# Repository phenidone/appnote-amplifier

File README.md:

# appnote-amplifier

This is a PCB design for a headphone amplifier based on the example schematic in the LME49600 datasheet.

## Power Supply

You will need a 12VAC or 24VAC centre-tapped transformer.  The simplest/safest option is to use it with
a Class-II (double insulated) accredited 12VAC 0.5A plugpack and not ground any part of this design.

Use Phoenix-style screw terminals.

## Inputs & Outputs

Place a 10K dual-gang A-scale volume pot between the signal source and the inputs to this board.  Use 0.1"-pitch
Phoenix-style screw terminals.

## Thermal

There is a bare patch on the board surrounding the output stage; you can solder a strip of copper
sheet here to act as a heatsink, if that seems to be necessary (almost certainly not).  Note that it will be connected to the negative
rail, so don't let the heatsink touch anything.

## Errata

Rev.A is missing reverse-protection diodes around the regulators.  They are considered best-practise
for cases where the input voltage on a regulator may collapse faster than its output and as such should not be necessary for this design - the regulators should be the only current
drain upon the rectifier capacitors.  They have been added to Rev.B on the basis of paranoia and can be hand-soldered onto the underside of a Rev.A board.

The BOM lists 7812 and 7912 regulators and 12VAC supply, which is more voltage than most headphones require.  For headphones of no more than 64 ohms,
a 7805 and 7905 are enough and will need only a 6VAC transformer.

## License

This hardware design is (C) 2017 William Brodie-Tyrrell and is licensed under the CERN OHL; see cern_ohl_v_1_2.pdf

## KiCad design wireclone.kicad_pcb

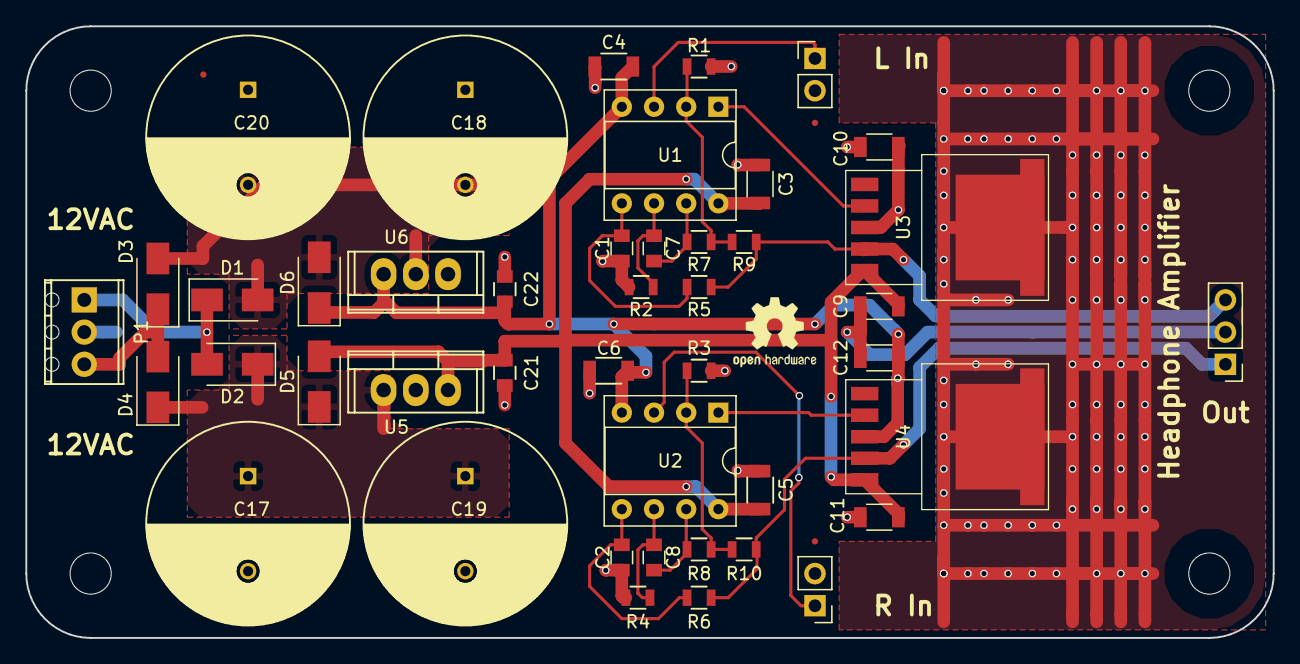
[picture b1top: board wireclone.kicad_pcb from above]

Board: 2 copper layers, 98.4 x 48.3 mm, 48 parts (0 on the bottom side), 21 nets.

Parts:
C1, C2, C7, C8: 1u; C_0805
C3, C4, C5, C6: 1u; C_1206
C9, C10, C11, C12: 10u; C_1206
C17, C18, C19, C20: 1000u; C_Radial_D16_L25_P7.5
C21, C22: 100n; C_0805
D1, D2, D3, D4, D5, D6: M7; D_SMA
FID1, FID2, FID3, FID4: FIDUCIAL; FID0.5
P1: CONN_01X03; TerminalBlock_Phoenix_MPT-2.54mm_3pol
P2, P4: CONN_01X02; Pin_Header_Straight_1x02_Pitch2.54mm
P3: CONN_01X03; Pin_Header_Straight_1x03_Pitch2.54mm
R1, R3, R7, R8, R9, R10: 1k; R_0805
R2, R4, R5, R6: 1M; R_0805
U1, U2: LME49720; DIP-8_W7.62mm_Socket
U3, U4: LME49600; TO-263-5
U5: LM7812CT; TO-220
U6: LM7912CT; TO-220

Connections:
/PSU/AC1: D3.1, D4.2, P1.3
/PSU/AC2: D1.1, D2.2, P1.1
/PSU/VCC: C3.2, C5.2, C9.2, C11.2, C21.1, D5.2, U1.8, U2.8, U3.5, U4.5, U5.3
/PSU/VEE: C4.2, C6.2, C10.2, C12.2, C22.2, D6.1, U1.4, U2.4, U3.3, U3.T, U4.3, U4.T, U6.3
/amplifiers/INL: P2.1, U1.3
/amplifiers/INR: P4.1, U2.3
/amplifiers/OUTL: P3.3, R5.1, R9.1, U3.4
/amplifiers/OUTR: P3.1, R6.1, R10.1, U4.4
GND: C1.1, C2.1, C3.1, C4.1, C5.1, C6.1, C9.1, C10.1, C11.1, C12.1, C17.2, C18.1, C19.2, C20.1, C21.2, C22.1, P1.2, P2.2, P3.2, P4.2, R1.2, R2.2, R3.2, R4.2, U5.2, U6.1
unnamed: C1.2, R5.2, U1.5
unnamed: C2.2, R6.2, U2.5
unnamed: C7.1, R7.2, U1.7
unnamed: C7.2, R2.1, U1.6
unnamed: C8.1, R8.2, U2.7
unnamed: C8.2, R4.1, U2.6
unnamed: C17.1, C19.1, D2.1, D4.1, D5.1, U5.1
unnamed: C18.2, C20.2, D1.2, D3.2, D6.2, U6.2
unnamed: R1.1, R7.1, R9.2, U1.2
unnamed: R3.1, R8.1, R10.2, U2.2
unnamed: U1.1, U3.2
unnamed: U2.1, U4.2

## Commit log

2016-12-07 begin schematic drafting - follows LME49600 datasheet
2017-10-24 checked in all subsheets
2017-10-24 second try adding
2017-10-25 did most of the layout
2017-10-25 moved output to end, stitched thermal plane
2017-10-26 complete layout drafted
2017-10-26 Beautification
2017-10-26 shortened board
2017-10-26 added fiducials
2017-10-28 cleanup, rev.a as manufactured
2017-10-28 added readme and license
2017-10-28 updated readme (grounding)
2017-10-28 added PDF of schematic
2017-12-27 added reverse protection diodes to regulators, bumped to Rev.B
2017-12-27 updated schematic.pdf
2017-12-27 updated schematic.pdf and README
2017-12-27 shrunk power connector, made all diodes same type, mentioned 5+5V operation in errata
